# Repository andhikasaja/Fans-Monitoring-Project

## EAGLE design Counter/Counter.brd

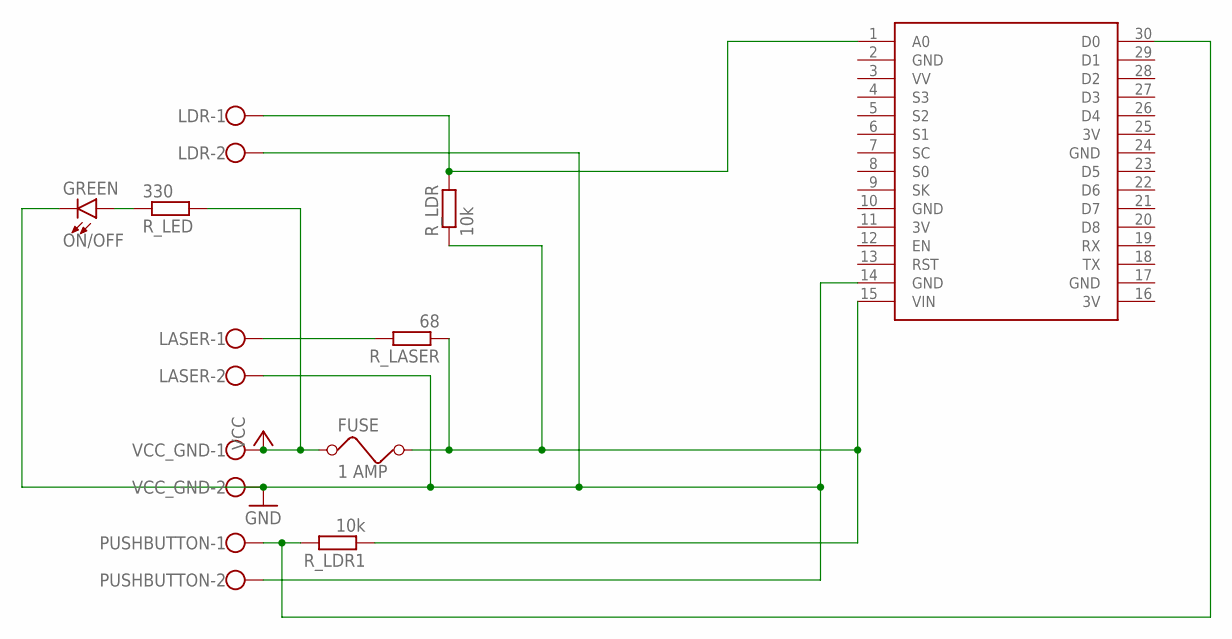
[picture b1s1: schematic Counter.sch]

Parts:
FUSE: 1 AMP; FUSE
LASER: W237-102
LDR: W237-102
ON/OFF: GREEN; LED_5MM
PUSHBUTTON: W237-102
R_LASER: 68; 0207/10
R_LDR, R_LDR1: 10k; 0207/10
R_LED: 330; 0207/10
U$1: NODEMCU
VCC_GND: W237-102

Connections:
3V: U$1.11 (3V), U$1.16 (3V), U$1.25 (3V)
GND: LASER.2, LDR.2, ON/OFF.K (C), PUSHBUTTON.2, U$1.2 (GND), U$1.10 (GND), U$1.14 (GND), U$1.17 (GND), U$1.24 (GND), VCC_GND.2
unnamed: LDR.1, R_LDR.2, U$1.1 (A0)
unnamed: LASER.1, R_LASER.2
unnamed: PUSHBUTTON.1, R_LDR1.2, U$1.30 (D0)
unnamed: ON/OFF.A, R_LED.1
unnamed: FUSE.2, R_LASER.1, R_LDR.1, R_LDR1.1, U$1.15 (VIN)
VCC: FUSE.1, R_LED.2, VCC_GND.1

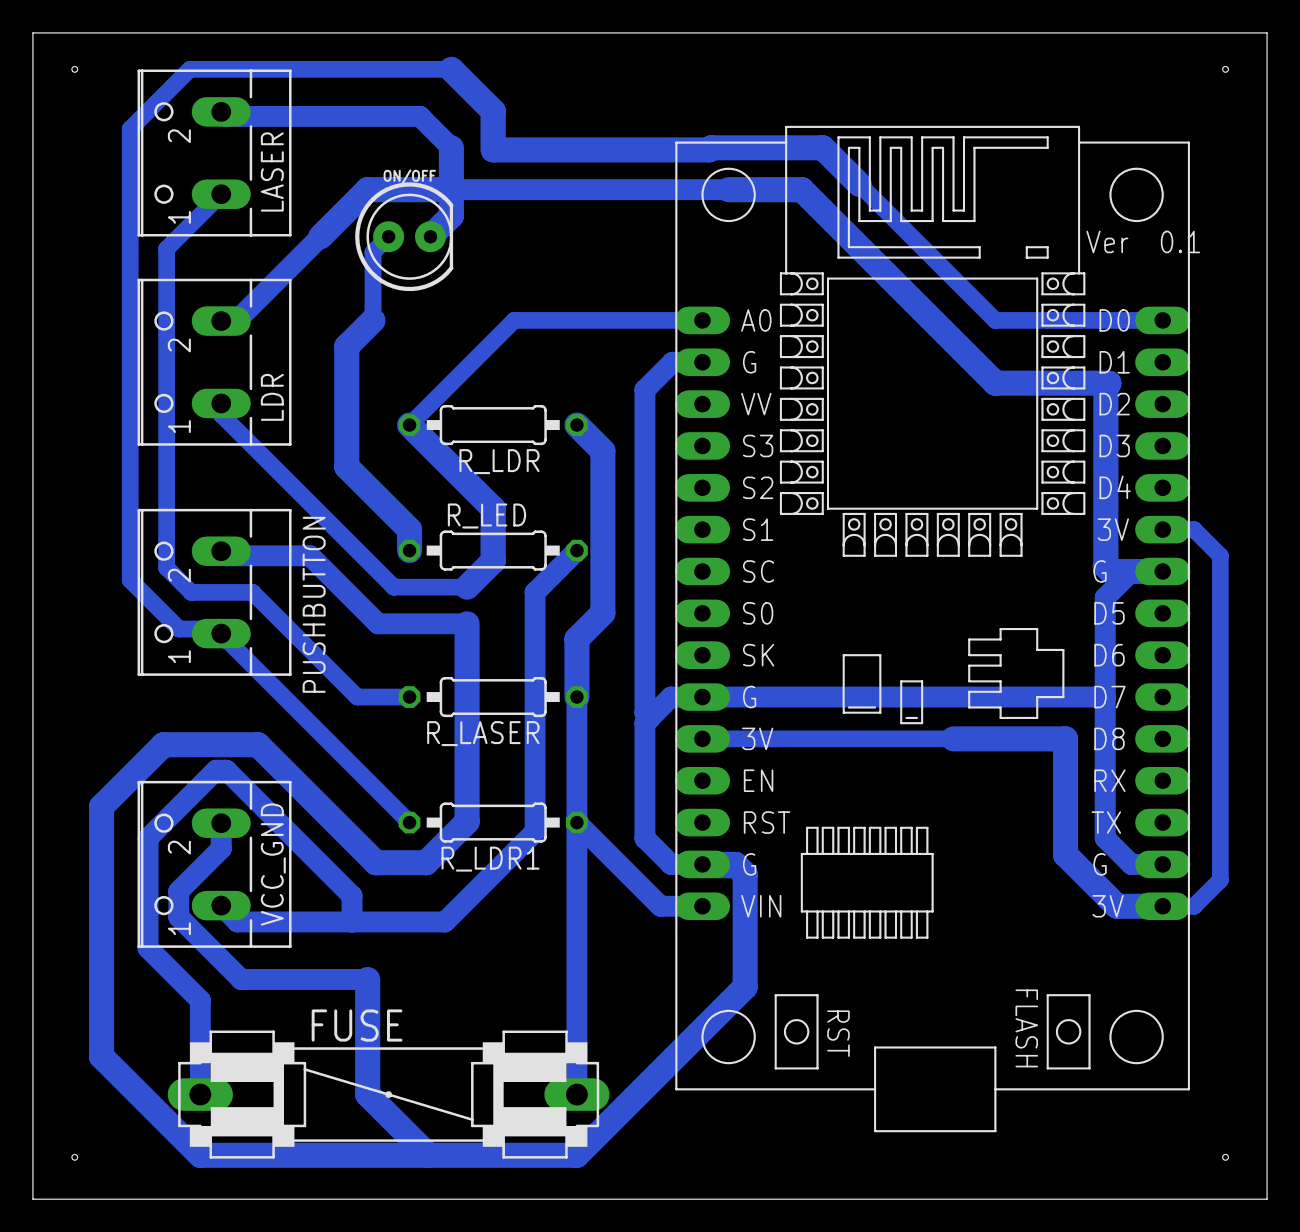
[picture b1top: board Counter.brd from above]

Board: 2 copper layers, 74.9 x 70.8 mm, 11 parts (0 on the bottom side), 8 nets.

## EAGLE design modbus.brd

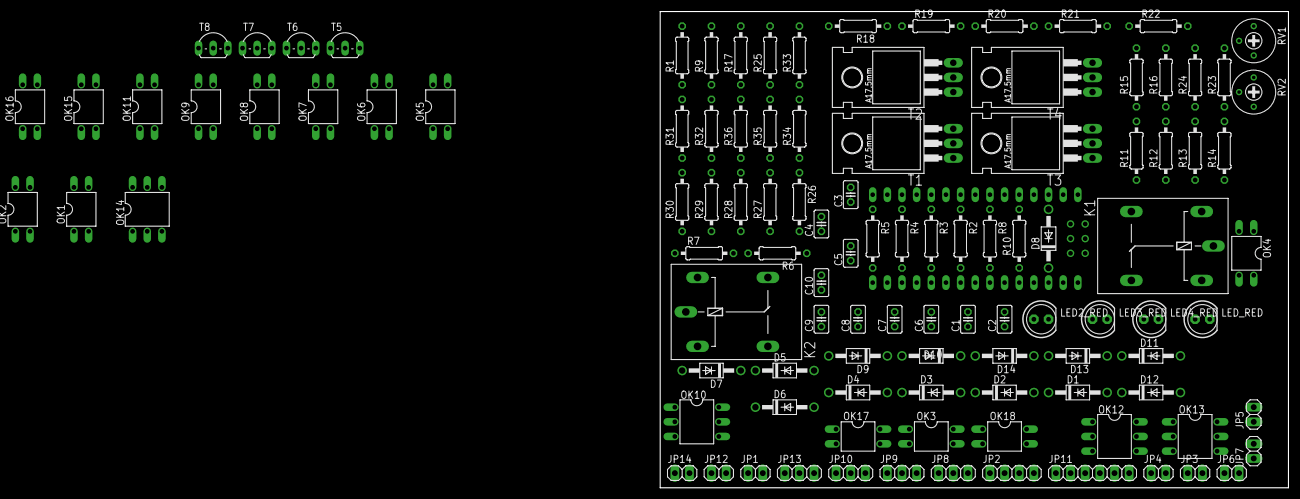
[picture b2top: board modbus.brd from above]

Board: 2 copper layers, 108.9 x 82.5 mm, 109 parts (0 on the bottom side), 103 nets, no tracks yet.

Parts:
C1, C2, C3, C4, C5, C6, C7, C8, C9, C10: 0.1 uF; C025-025X050
D1, D2, D3, D4, D5, D6, D7, D8, D9, D10, D11, D12, D13, D14: 1N4004; DO41-10
JP1, JP12, JP14: 1X02
JP2: 1X04
JP3, JP4, JP5: 1.N 2.L; 1X02
JP6: 1.N 2. L; 1X02
JP7: 1.N 2.220VAC; 1X02
JP8, JP9, JP10, JP13: 1X03
JP11: 1X06
K1, K2: G5LE
LED2_RED, LED3_RED, LED4_RED: LED5MM
LED_RED: LED5MM
OK1, OK2, OK3, OK4, OK5, OK6, OK7, OK8, OK9, OK11, OK15, OK16, OK17, OK18: PC817; DIL04
OK10, OK12, OK13, OK14: MOC3021M; DIL06
R1, R2, R3, R4, R5, R6, R7, R8, R10: 10k; 0207/10
R9: 0207/10
R11, R12, R13, R14, R19, R20, R21, R22: 470; 0207/10
R15, R16, R17, R18: 330; 0207/10
R23, R24, R25, R26, R27, R28, R29, R30, R31, R32, R33, R34, R35, R36: 1k; 0207/10
RV1, RV2: 1k; RTRIM3339P
T1, T2, T3, T4: BT136; TO220AB
T5, T6, T7, T8: 2N2222; TO92-EBC-OVAL
U$1: NANO

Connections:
GND: C1.2, C2.2, C3.2, C4.2, C5.2, C6.2, C7.2, C8.2, C9.2, C10.2, JP1.2, JP2.2, JP14.2, OK1.3, OK2.3, OK3.3, OK4.3, OK5.3, OK6.3, OK7.3, OK8.3, OK9.3, OK10.2, OK11.3, OK12.2, OK13.2, OK14.2, OK15.2, OK16.2, OK17.2, OK18.2, RV1.1, RV2.1, T5.E, T6.E, T7.E, T8.E
unnamed: JP8.1, K1.O
unnamed: C1.1, OK1.4, R1.1, U$1.D2
unnamed: C2.1, OK2.4, R2.1, U$1.D3
unnamed: C3.1, OK3.4, R3.1, U$1.D4
unnamed: C4.1, OK4.4, R4.1, U$1.D5
unnamed: C5.1, OK5.4, R5.1, U$1.D6
unnamed: C6.1, OK6.4, R6.1, U$1.D7
unnamed: C7.1, OK7.4, R7.1, U$1.D8
unnamed: C8.1, OK8.4, R8.1, U$1.D9
unnamed: C9.1, OK9.4, R9.1, U$1.D10
unnamed: C10.1, OK11.4, R10.1, U$1.D11
unnamed: JP2.3, U$1.RX1
unnamed: JP2.4, U$1.TX0
unnamed: RV2.2, U$1.A6
unnamed: RV1.2, U$1.A7
unnamed: LED_RED.K, OK10.1
unnamed: LED2_RED.K, OK12.1
unnamed: LED3_RED.K, OK13.1
unnamed: LED4_RED.K, OK14.1
unnamed: LED_RED.A, R11.2
unnamed: LED2_RED.A, R12.2
unnamed: LED3_RED.A, R13.2
unnamed: LED4_RED.A, R14.2
unnamed: R11.1, U$1.A5
unnamed: R12.1, U$1.A4
unnamed: R13.1, U$1.A3
unnamed: R14.1, U$1.A2
unnamed: R17.1, U$1.A0
unnamed: R15.1, U$1.D12
unnamed: R16.1, U$1.D13
unnamed: R18.1, U$1.A1
unnamed: OK18.1, R15.2
unnamed: OK17.1, R16.2
unnamed: OK16.1, R17.2
unnamed: OK15.1, R18.2
unnamed: OK10.6, R19.2
unnamed: JP3.2, R19.1, T1.2
unnamed: JP4.2, R20.1, T2.2
unnamed: JP5.2, R21.1, T3.2
unnamed: JP6.2, R22.1, T4.2
unnamed: OK12.4, T2.3
unnamed: OK12.6, R20.2
unnamed: OK13.6, R21.2
unnamed: OK13.4, T3.3
unnamed: OK14.4, T4.3
unnamed: OK14.6, R22.2
unnamed: JP8.2, K1.P
unnamed: JP7.2, T1.1, T2.1, T3.1, T4.1
unnamed: D1.A, OK15.3
unnamed: D2.A, OK16.3
unnamed: D2.C, R24.1
unnamed: JP3.1, JP4.1, JP5.1, JP6.1, JP7.1
unnamed: D1.C, R23.1
unnamed: R23.2, T5.B
unnamed: R24.2, T6.B
unnamed: JP8.3, K1.S
unnamed: K1.2, T5.C
unnamed: K2.1, T6.C
unnamed: JP9.1, K2.O
unnamed: JP9.2, K2.P
unnamed: JP9.3, K2.S
unnamed: OK18.3, R26.1
unnamed: OK17.3, R25.1
unnamed: JP10.1, OK17.4, OK18.4
unnamed: D3.A, R25.2
unnamed: D4.A, R26.2
unnamed: D3.C, T7.B
unnamed: D4.C, T8.B
unnamed: JP10.2, T7.C
unnamed: JP10.3, T8.C
unnamed: OK1.1, R36.1
unnamed: OK2.1, R35.1
unnamed: OK3.1, R34.1
unnamed: OK4.1, R33.1
unnamed: OK5.1, R32.1
unnamed: OK6.1, R31.1
unnamed: OK7.1, R30.1
unnamed: OK8.1, R29.1
unnamed: OK9.1, R28.1
unnamed: OK11.1, R27.1
unnamed: R1.2, R2.2, R3.2, R4.2, R5.2, R6.2, R7.2, R8.2, R9.2, R10.2
unnamed: D5.C, JP11.5
unnamed: D6.C, JP11.4
unnamed: D7.C, JP11.3
unnamed: D8.C, JP11.2
unnamed: D9.C, JP11.1
unnamed: D10.C, JP12.2
unnamed: D11.C, JP12.1
unnamed: D12.C, JP13.3
unnamed: D13.C, JP13.2
unnamed: D14.C, JP13.1
unnamed: D14.A, OK11.2
unnamed: D13.A, OK9.2
unnamed: D12.A, OK8.2
unnamed: D11.A, OK7.2
unnamed: D10.A, OK6.2
unnamed: D9.A, OK5.2
unnamed: D8.A, OK4.2
unnamed: D7.A, OK3.2
unnamed: D6.A, OK2.2
unnamed: D5.A, OK1.2
VCC: JP1.1, JP2.1, JP14.1, K1.1, K2.2, OK15.4, OK16.4, R27.2, R28.2, R29.2, R30.2, R31.2, R32.2, R33.2, R34.2, R35.2, R36.2, RV1.3, RV2.3

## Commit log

2019-10-31 modul modbus dg arduino nano
2019-10-31 board desain untuk modul modbus
2019-11-12 final untuk pembacaan kecepatan konveyor dan pengiriman ke server
2019-11-21 board & skematik speed sensor dan counter sudah siap
2019-11-24 perubahan skematik counter. Penambahan terminal block
2019-11-28 revisi rangkaian rev 3 + penambahan reset
2019-12-02 penambahan fuse dan lampu indikator pada board, pembuatan masking. penambahan program counter
2019-12-04 penambahan reset counter
2019-12-05 rev 6, perbaikan di counter
2019-12-06 rev 6 speed sensor, pemindahan data ke D2 / GPIO 4

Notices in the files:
parts and their libraries:
SparkFun-LED: Licensing: Creative Commons ShareAlike 4.0 International - https://creativecommons.org/licenses/by-sa/4.0
